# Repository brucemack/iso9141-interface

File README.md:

Overview
========
This is a KiCad project for a simple ISO-9141 interface board.  This allows a microcontroller to be interfaced to car's ISO-9141 (OBD2) port.

Please see related firmware projects:

* [The OBDII Reader](https://github.com/brucemack/hello-obd2)
* [The ECU Simulator](https://github.com/brucemack/ecu-sim)

[Here is the official ISO standard document](https://cdn.standards.iteh.ai/samples/16737/e6b719fd44c345a792656f6d19e6cee4/ISO-9141-1989.pdf) that explains all of the details of this interface. What makes this interesting is that the transmit/receive to/from the vehicle all happens on a single wire.

Send any questions to bruce at mackinnon dot com.

Interfaces (V2)
===============

J1 is the connection to the vehicle:
* Pin 1 - 12V battery power
* Pin 2 - KLINE
* Pin 3 - Ground

J2 is the connector to the microcontroller:
* Pin 1 - Data transmit (data from controller to vehicle)
* Pin 2 - Data receive (data from vehicle to controller)
* Pin 3 - Control line which allow the KLINE to be pulled low for the purposes of signalling
* Pin 4 - An indicator LED that can be used by the controller
* Pin 5 - +5V regulated power for controller
* Pin 6 - Ground

Hardware
========

The V2 PCB:

Here's what it looks like in real life (V1):

Connector Notes
===============

The scanner/instrument uses a SAE J1962 connector (male)
* [Cable](https://www.amazon.com/iKKEGOL-Connector-Diagnostic-Extension-Pigtail/dp/B0828YHWFG)
* [Just the Connector](https://www.sparkfun.com/products/9911)
* [Connector](https://www.amazon.com/Elecbee-Automobile-Connector-Shell-Diagnostic/dp/B0CKMSXCBY)

The vehicle uses a J1962F female connector like this: https://www.amazon.com/Goliton-Connection-Connector-Harness-Assembled/dp/B09NBWQLMQ

Copyright
=========

Copyright (C) 2024 - Bruce MacKinnon

This work is covered under the terms of the GNU Public License (V3). Please consult the LICENSE file for more information.

This work is being made available for non-commercial use. Redistribution, commercial use or sale of any part is prohibited.

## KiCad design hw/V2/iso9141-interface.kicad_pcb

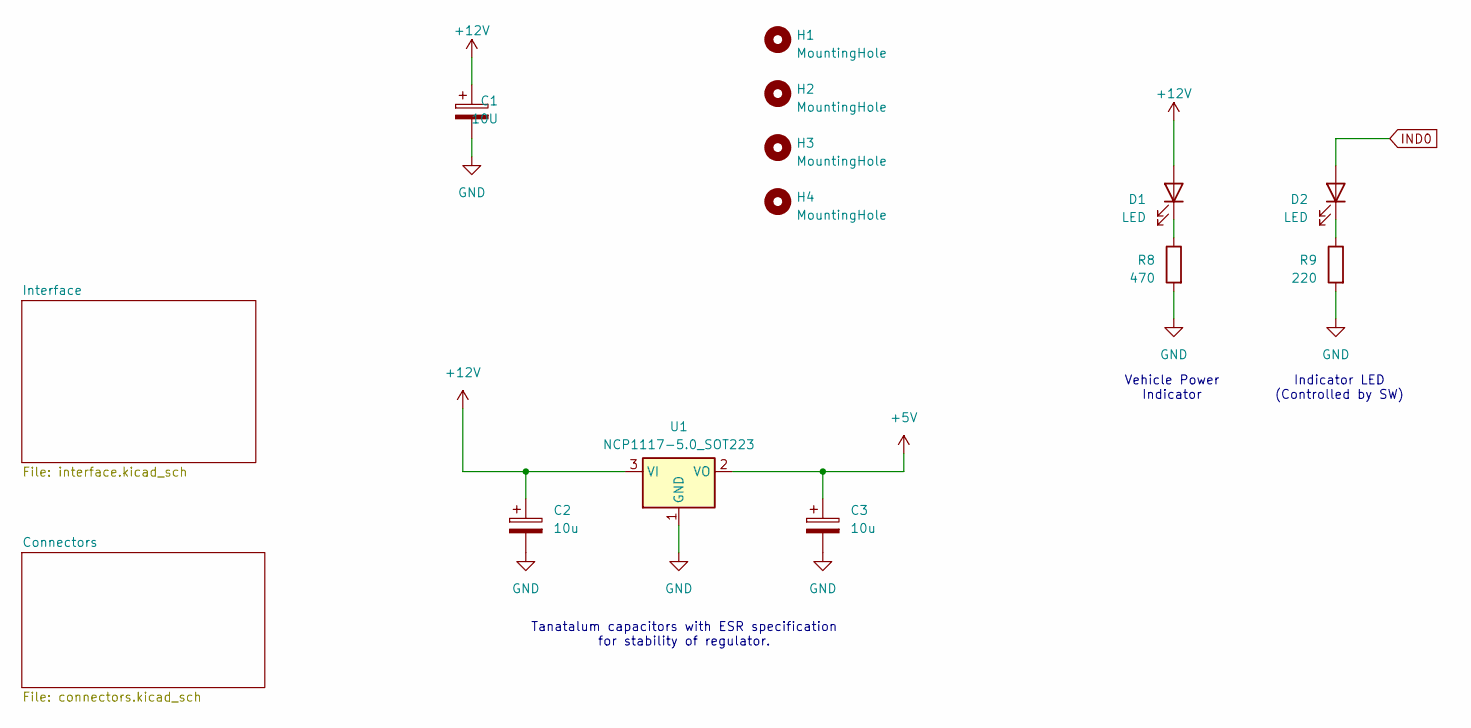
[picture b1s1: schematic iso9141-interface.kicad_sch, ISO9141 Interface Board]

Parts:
C1: 10U; CPOL_0805_2012Metric_Pad1.18x1.45mm_HandSolder
C2, C3: 10u; CPOL_0805_2012Metric_Pad1.18x1.45mm_HandSolder
D1, D2: LED; LED_0805_2012Metric_Pad1.15x1.40mm_HandSolder
H1, H2, H3, H4: MountingHole; MountingHole_4.3mm_M4
R8: 470; R_0805_2012Metric_Pad1.20x1.40mm_HandSolder
R9: 220; R_0805_2012Metric_Pad1.20x1.40mm_HandSolder
U1: NCP1117-5.0_SOT223; SOT-223-3_TabPin2

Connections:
+5V: C3.1, U1.2 (VO); also elsewhere on the board
+12V: C1.1, C2.1, D1.2 (A), U1.3 (VI); also elsewhere on the board
GND: C1.2, C2.2, C3.2, R8.2, R9.2, U1.1 (GND); also elsewhere on the board
IND0: D2.2 (A); also elsewhere on the board
unnamed: D1.1 (K), R8.1
unnamed: D2.1 (K), R9.1

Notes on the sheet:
Tanatalum capacitors with ESR specification for stability of regulator.
Indicator LED (Controlled by SW)
Vehicle Power Indicator

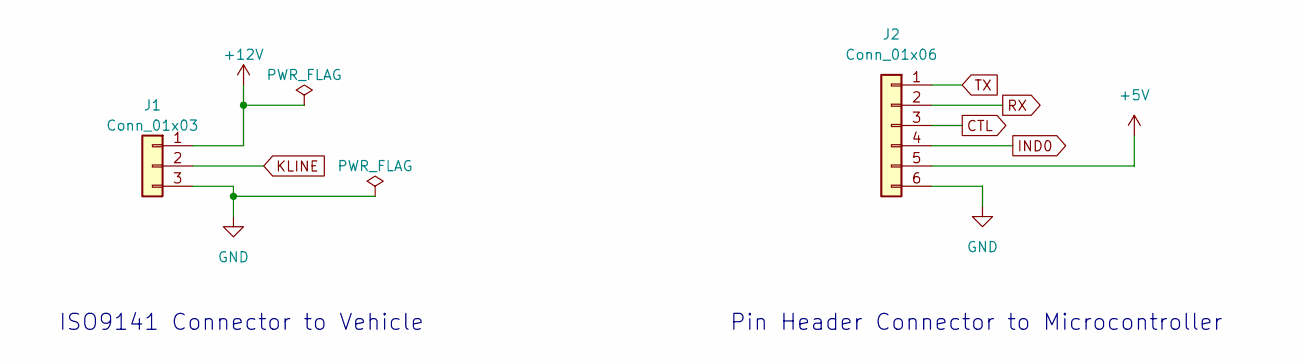
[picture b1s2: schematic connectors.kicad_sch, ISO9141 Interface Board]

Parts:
J1: Conn_01x03; PinHeader_1x03_P2.54mm_Vertical
J2: Conn_01x06; PinHeader_1x06_P2.54mm_Vertical

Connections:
+5V: J2.5; also elsewhere on the board
+12V: J1.1; also elsewhere on the board
CTL: J2.3; also elsewhere on the board
GND: J1.3, J2.6; also elsewhere on the board
IND0: J2.4; also elsewhere on the board
KLINE: J1.2; also elsewhere on the board
RX: J2.2; also elsewhere on the board
TX: J2.1; also elsewhere on the board

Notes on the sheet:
Pin Header Connector to Microcontroller
ISO9141 Connector to Vehicle

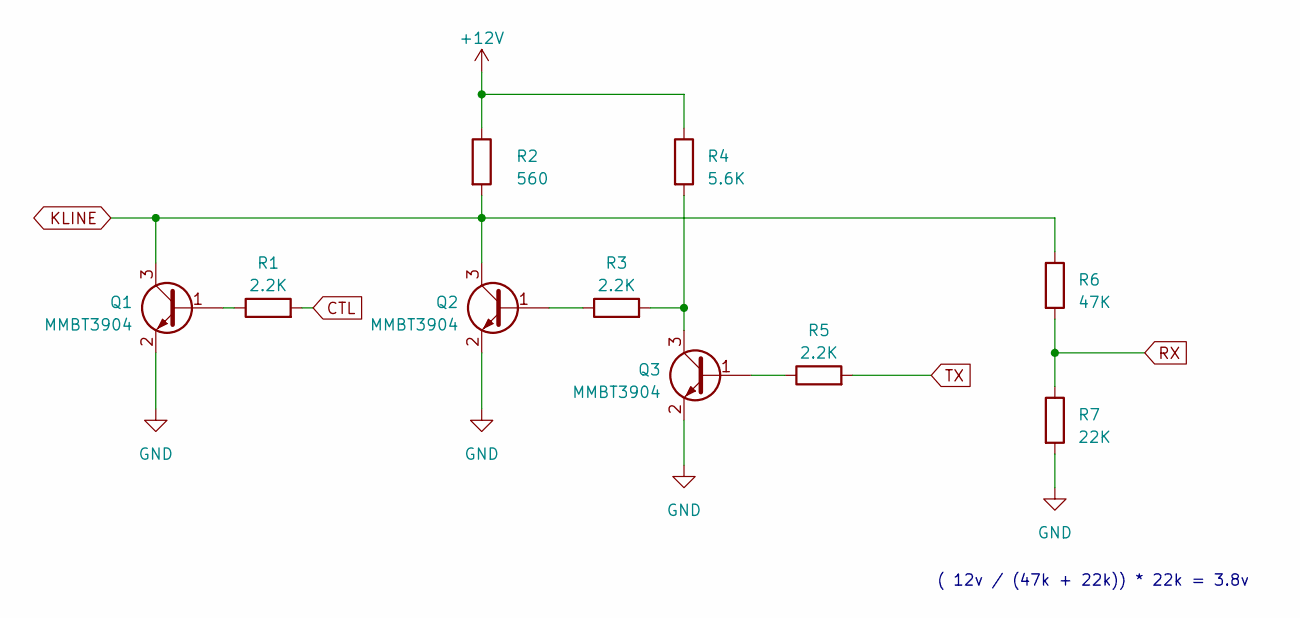
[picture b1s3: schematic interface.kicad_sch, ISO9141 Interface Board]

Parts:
Q1, Q2, Q3: MMBT3904; SOT-23
R1, R3, R5: 2.2K; R_0805_2012Metric_Pad1.20x1.40mm_HandSolder
R2: 560; R_0805_2012Metric_Pad1.20x1.40mm_HandSolder
R4: 5.6K; R_0805_2012Metric_Pad1.20x1.40mm_HandSolder
R6: 47K; R_0805_2012Metric_Pad1.20x1.40mm_HandSolder
R7: 22K; R_0805_2012Metric_Pad1.20x1.40mm_HandSolder

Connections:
+12V: R2.1, R4.1; also elsewhere on the board
CTL: R1.2; also elsewhere on the board
GND: Q1.2 (E), Q2.2 (E), Q3.2 (E), R7.2; also elsewhere on the board
KLINE: Q1.3 (C), Q2.3 (C), R2.2, R6.1; also elsewhere on the board
unnamed: Q1.1 (B), R1.1
unnamed: Q2.1 (B), R3.1
unnamed: Q3.1 (B), R5.1
unnamed: Q3.3 (C), R3.2, R4.2
RX: R6.2, R7.1; also elsewhere on the board
TX: R5.2; also elsewhere on the board

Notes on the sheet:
( 12v / (47k + 22k)) * 22k = 3.8v

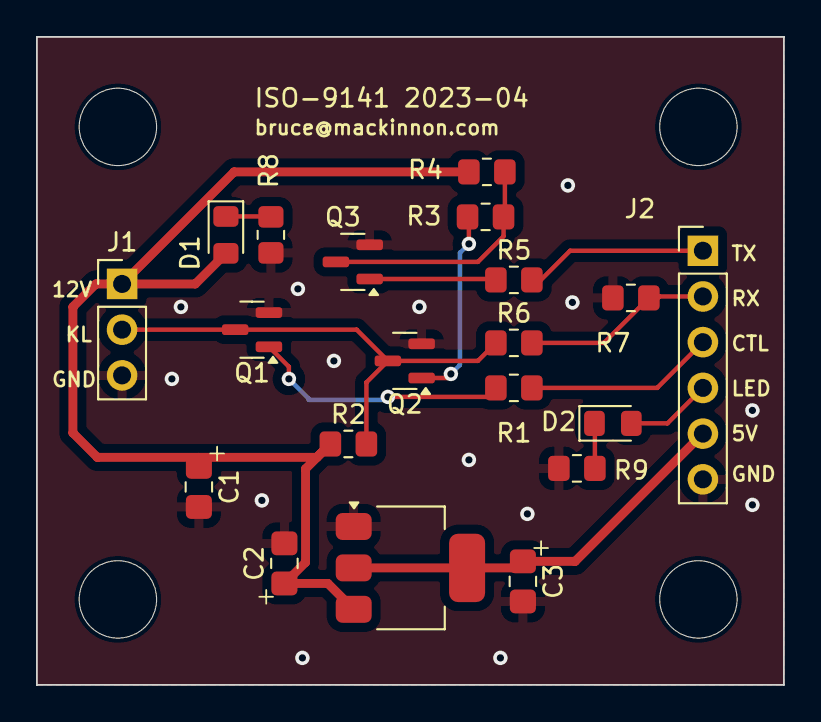
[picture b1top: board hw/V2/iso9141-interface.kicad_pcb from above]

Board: 2 copper layers, 41.5 x 36.0 mm, 24 parts (0 on the bottom side), 14 nets.

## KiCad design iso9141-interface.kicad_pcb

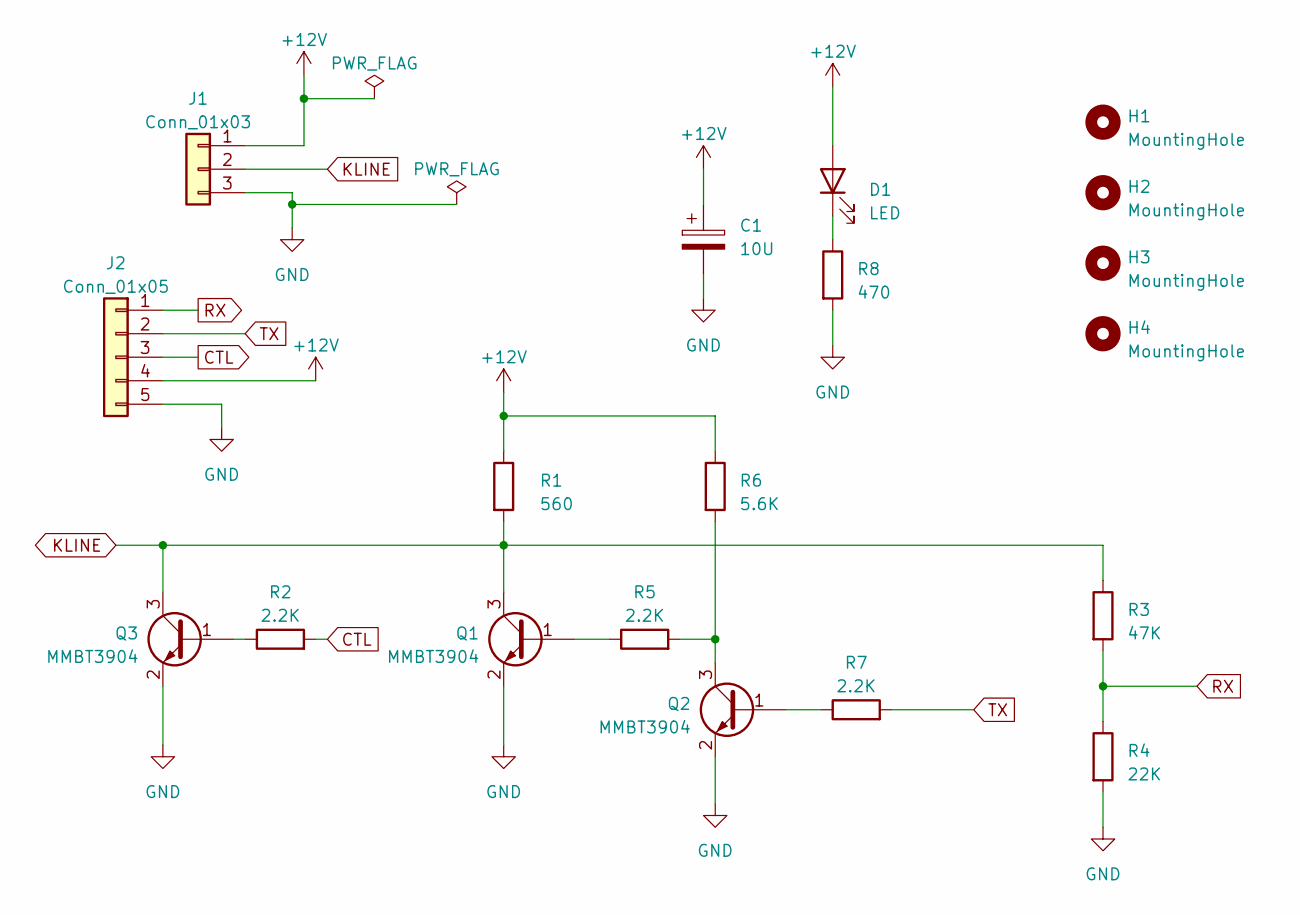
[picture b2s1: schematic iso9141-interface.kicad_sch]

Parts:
C1: 10U; C_1206_3216Metric_Pad1.33x1.80mm_HandSolder
D1: LED; LED_1206_3216Metric_Pad1.42x1.75mm_HandSolder
H1, H2, H3, H4: MountingHole; MountingHole_4.3mm_M4
J1: Conn_01x03; PinHeader_1x03_P2.54mm_Vertical
J2: Conn_01x05; PinHeader_1x05_P2.54mm_Vertical
Q1, Q2, Q3: MMBT3904; SOT-23
R1: 560; R_0805_2012Metric_Pad1.20x1.40mm_HandSolder
R2, R5, R7: 2.2K; R_0805_2012Metric_Pad1.20x1.40mm_HandSolder
R3: 47K; R_0805_2012Metric_Pad1.20x1.40mm_HandSolder
R4: 22K; R_0805_2012Metric_Pad1.20x1.40mm_HandSolder
R6: 5.6K; R_0805_2012Metric_Pad1.20x1.40mm_HandSolder
R8: 470; R_0805_2012Metric_Pad1.20x1.40mm_HandSolder

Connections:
+12V: C1.1, D1.2 (A), J1.1, J2.4, R1.1, R6.1
CTL: J2.3, R2.2
GND: C1.2, J1.3, J2.5, Q1.2 (E), Q2.2 (E), Q3.2 (E), R4.2, R8.2
KLINE: J1.2, Q1.3 (C), Q3.3 (C), R1.2, R3.1
unnamed: D1.1 (K), R8.1
unnamed: Q1.1 (B), R5.1
unnamed: Q2.1 (B), R7.1
unnamed: Q2.3 (C), R5.2, R6.2
unnamed: Q3.1 (B), R2.1
RX: J2.1, R3.2, R4.1
TX: J2.2, R7.2

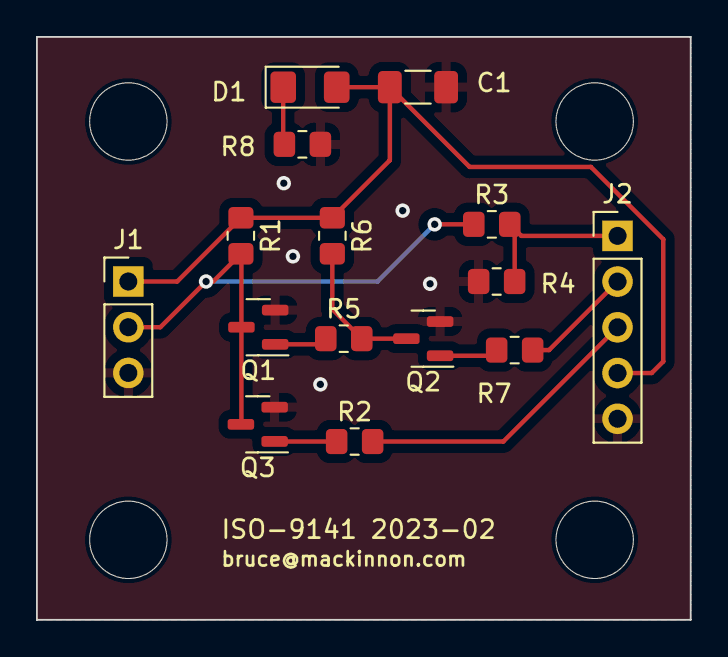
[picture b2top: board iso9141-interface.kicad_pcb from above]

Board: 2 copper layers, 36.3 x 32.4 mm, 19 parts (0 on the bottom side), 11 nets.

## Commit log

2023-02-20 Working
2023-03-08 Improved docs
2024-04-17 Commiting V2 files that were previously missing
2024-04-17 Pushed up most recent documentation
2024-04-19 Updated PCB for V2, sent to JLC
2024-04-20 Added docs for Nano demo
2024-04-20 GPLv3

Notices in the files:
hw/V2/connectors.kicad_sch:
Copyright (C) Bruce MacKinnon - NOT FOR COMMERCIAL USE
